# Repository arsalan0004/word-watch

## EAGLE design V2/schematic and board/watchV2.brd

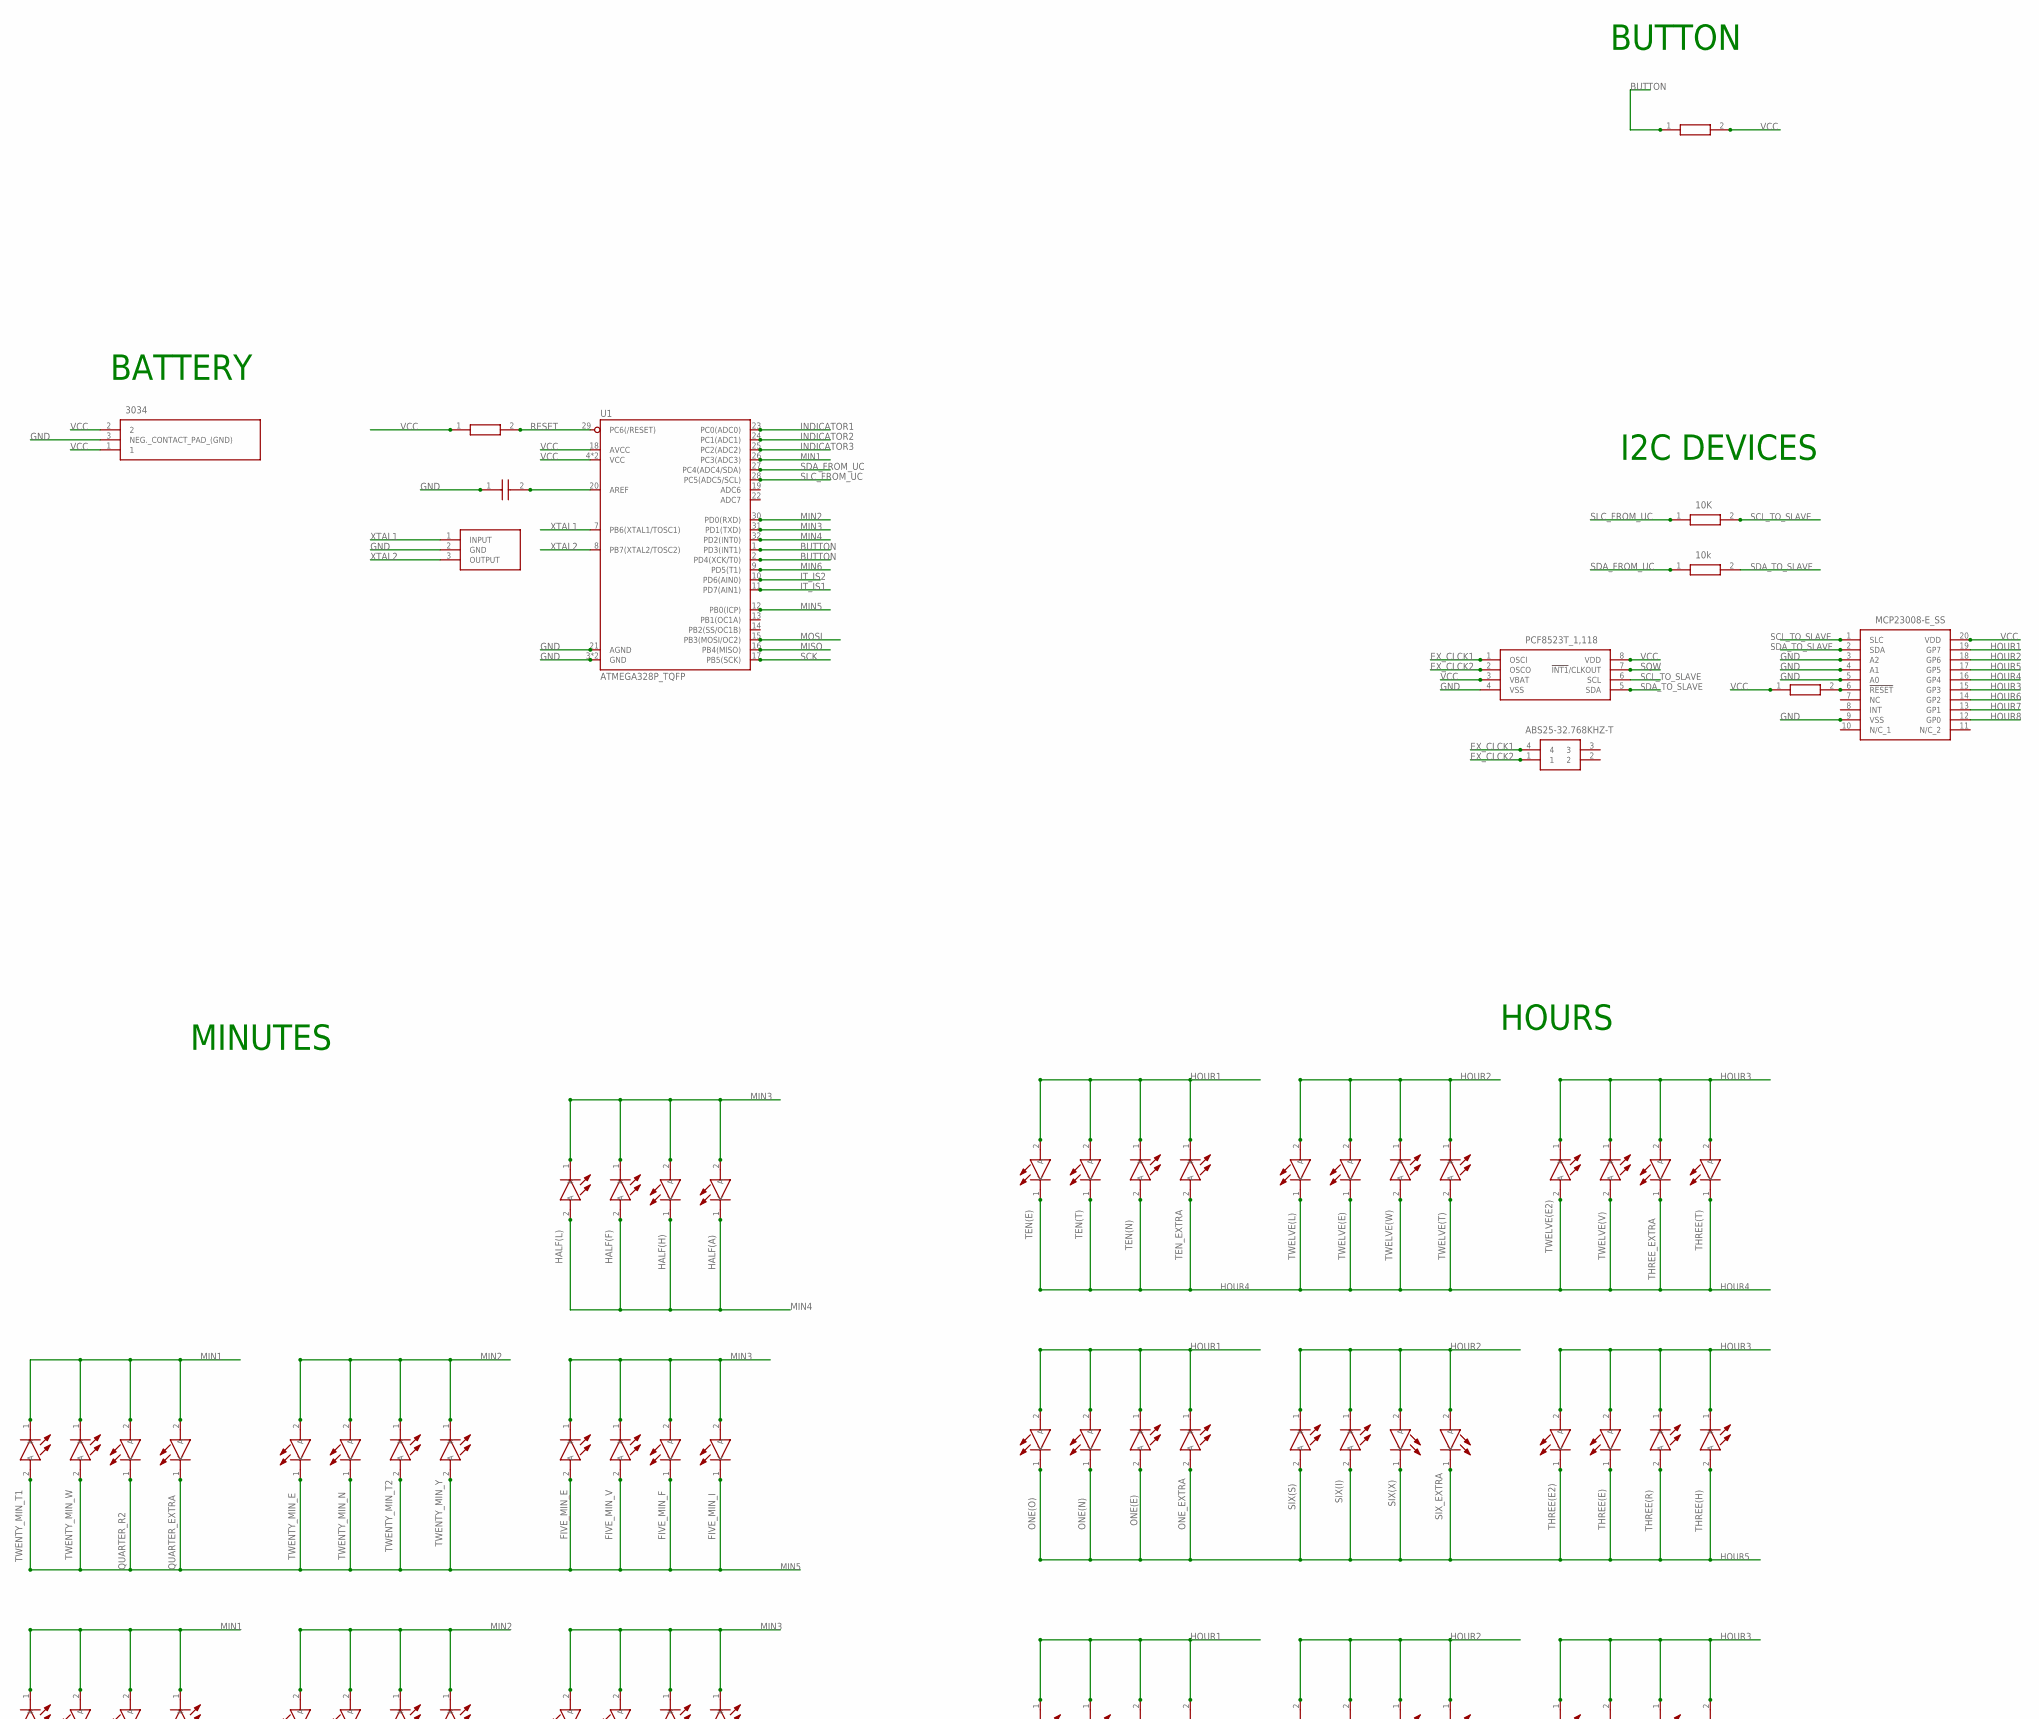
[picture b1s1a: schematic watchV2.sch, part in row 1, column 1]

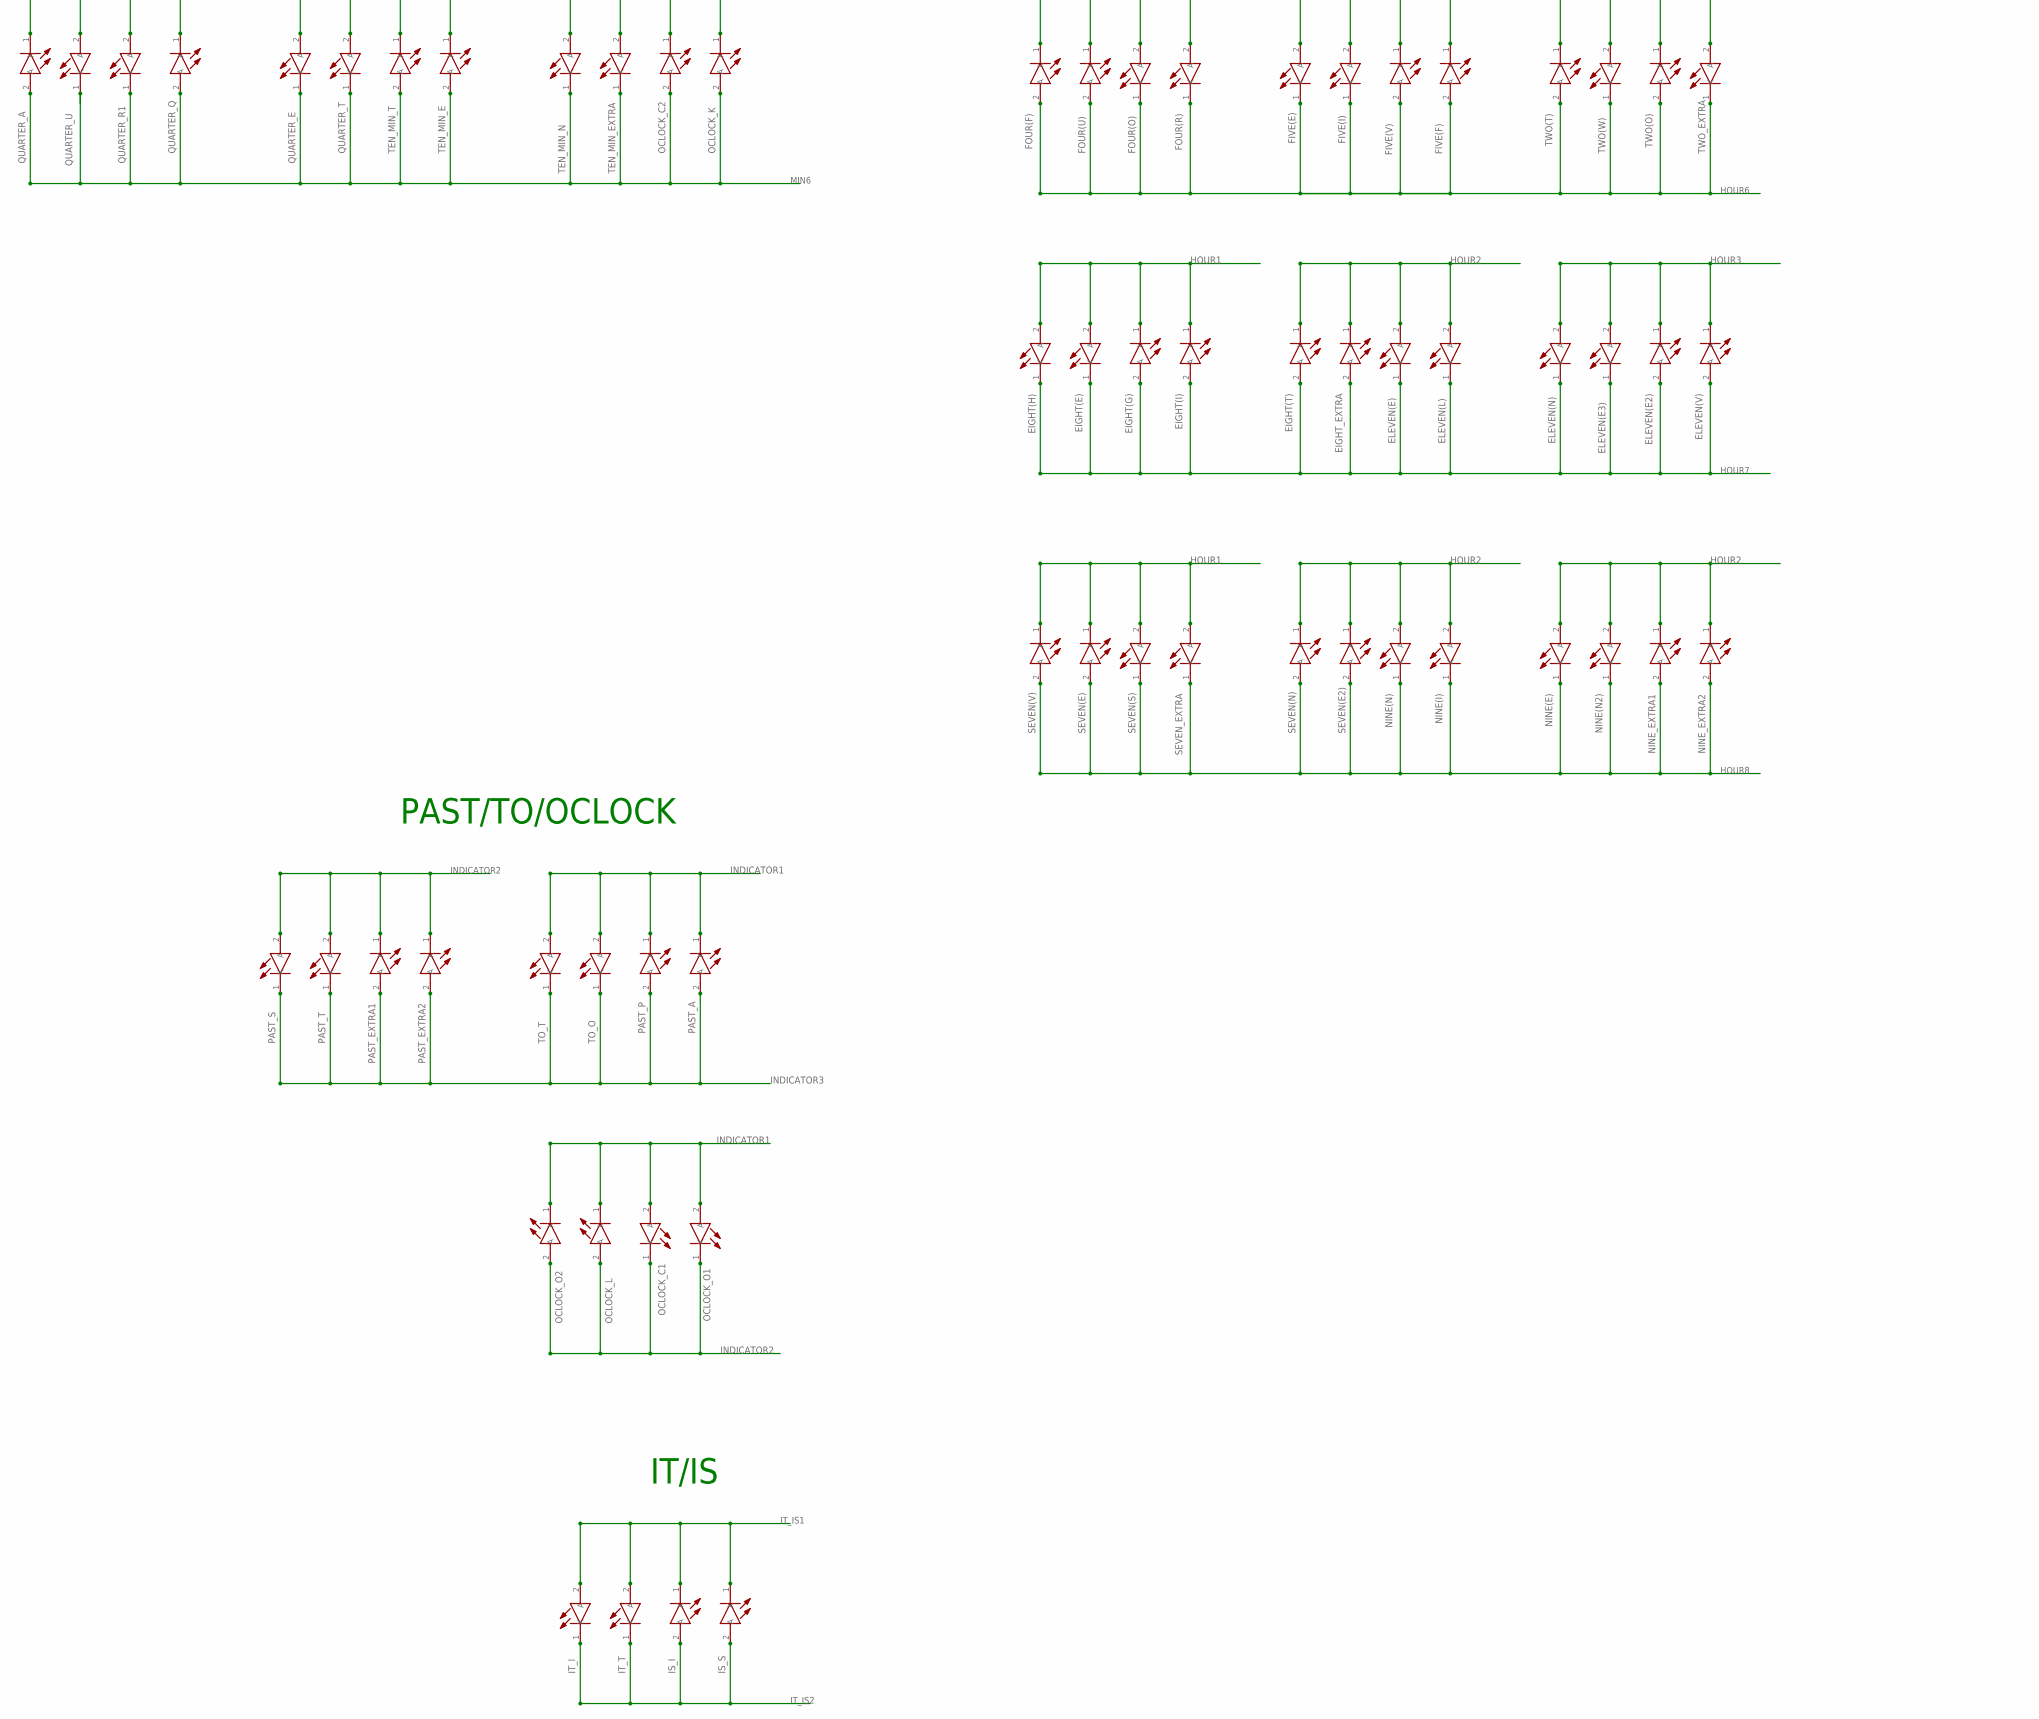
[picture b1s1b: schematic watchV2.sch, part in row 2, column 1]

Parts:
10K: RC0402FR-0722RL; RESC1005X40N
C1: C0402C104Z4VAC; CAPC1005X55N
EIGHT(E): APHHS1005CGCK; LEDC1005X60N
EIGHT(G): APHHS1005CGCK; LEDC1005X60N
EIGHT(H): APHHS1005CGCK; LEDC1005X60N
EIGHT(I): APHHS1005CGCK; LEDC1005X60N
EIGHT(T): APHHS1005CGCK; LEDC1005X60N
EIGHT_EXTRA: APHHS1005CGCK; LEDC1005X60N
ELEVEN(E2), ELEVEN(E3): APHHS1005CGCK; LEDC1005X60N
ELEVEN(E): APHHS1005CGCK; LEDC1005X60N
ELEVEN(L): APHHS1005CGCK; LEDC1005X60N
ELEVEN(N): APHHS1005CGCK; LEDC1005X60N
ELEVEN(V): APHHS1005CGCK; LEDC1005X60N
FIVE(E): APHHS1005CGCK; LEDC1005X60N
FIVE(F): APHHS1005CGCK; LEDC1005X60N
FIVE(I): APHHS1005CGCK; LEDC1005X60N
FIVE(V): APHHS1005CGCK; LEDC1005X60N
FIVE_MIN_E: APHHS1005CGCK; LEDC1005X60N
FIVE_MIN_F: APHHS1005CGCK; LEDC1005X60N
FIVE_MIN_I: APHHS1005CGCK; LEDC1005X60N
FIVE_MIN_V: APHHS1005CGCK; LEDC1005X60N
FOUR(F): APHHS1005CGCK; LEDC1005X60N
FOUR(O): APHHS1005CGCK; LEDC1005X60N
FOUR(R): APHHS1005CGCK; LEDC1005X60N
FOUR(U): APHHS1005CGCK; LEDC1005X60N
HALF(A): APHHS1005CGCK; LEDC1005X60N
HALF(F): APHHS1005CGCK; LEDC1005X60N
HALF(H): APHHS1005CGCK; LEDC1005X60N
HALF(L): APHHS1005CGCK; LEDC1005X60N
IC1: MCP23008-E_SS; SOP65P780X200-20N
IC2: CSTNE16M0VH3C000R0
IC3: PCF8523T_1,118; SOIC127P600X175-8N
IS_I: APHHS1005CGCK; LEDC1005X60N
IS_S: APHHS1005CGCK; LEDC1005X60N
IT_I: APHHS1005CGCK; LEDC1005X60N
IT_T: APHHS1005CGCK; LEDC1005X60N
NINE(E): APHHS1005CGCK; LEDC1005X60N
NINE(I): APHHS1005CGCK; LEDC1005X60N
NINE(N2): APHHS1005CGCK; LEDC1005X60N
NINE(N): APHHS1005CGCK; LEDC1005X60N
NINE_EXTRA1, NINE_EXTRA2: APHHS1005CGCK; LEDC1005X60N
OCLOCK_C1, OCLOCK_C2: APHHS1005CGCK; LEDC1005X60N
OCLOCK_K: APHHS1005CGCK; LEDC1005X60N
OCLOCK_L: APHHS1005CGCK; LEDC1005X60N
OCLOCK_O1, OCLOCK_O2: APHHS1005CGCK; LEDC1005X60N
ONE(E): APHHS1005CGCK; LEDC1005X60N
ONE(N): APHHS1005CGCK; LEDC1005X60N
ONE(O): APHHS1005CGCK; LEDC1005X60N
ONE_EXTRA: APHHS1005CGCK; LEDC1005X60N
PAST_A: APHHS1005CGCK; LEDC1005X60N
PAST_EXTRA1: 48ohm; LEDC1005X60N
PAST_EXTRA2: APHHS1005CGCK; LEDC1005X60N
PAST_P: 48ohm; LEDC1005X60N
PAST_S: APHHS1005CGCK; LEDC1005X60N
PAST_T: APHHS1005CGCK; LEDC1005X60N
QUARTER_A: APHHS1005CGCK; LEDC1005X60N
QUARTER_E: APHHS1005CGCK; LEDC1005X60N
QUARTER_EXTRA: APHHS1005CGCK; LEDC1005X60N
QUARTER_Q: APHHS1005CGCK; LEDC1005X60N
QUARTER_R1, QUARTER_R2: APHHS1005CGCK; LEDC1005X60N
QUARTER_T: APHHS1005CGCK; LEDC1005X60N
QUARTER_U: APHHS1005CGCK; LEDC1005X60N
RED1, RED2, RED5: RC0402FR-0722RL; RESC1005X40N
RED7: 10k; RESC1005X40N
SEVEN(E2): APHHS1005CGCK; LEDC1005X60N
SEVEN(E): APHHS1005CGCK; LEDC1005X60N
SEVEN(N): APHHS1005CGCK; LEDC1005X60N
SEVEN(S): APHHS1005CGCK; LEDC1005X60N
SEVEN(V): APHHS1005CGCK; LEDC1005X60N
SEVEN_EXTRA: APHHS1005CGCK; LEDC1005X60N
SIX(I): APHHS1005CGCK; LEDC1005X60N
SIX(S): APHHS1005CGCK; LEDC1005X60N
SIX(X): APHHS1005CGCK; LEDC1005X60N
SIX_EXTRA: APHHS1005CGCK; LEDC1005X60N
TEN(E): APHHS1005CGCK; LEDC1005X60N
TEN(N): APHHS1005CGCK; LEDC1005X60N
TEN(T): APHHS1005CGCK; LEDC1005X60N
TEN_EXTRA: APHHS1005CGCK; LEDC1005X60N
TEN_MIN_E: APHHS1005CGCK; LEDC1005X60N
TEN_MIN_EXTRA: APHHS1005CGCK; LEDC1005X60N
TEN_MIN_N: APHHS1005CGCK; LEDC1005X60N
TEN_MIN_T: APHHS1005CGCK; LEDC1005X60N
THREE(E2): APHHS1005CGCK; LEDC1005X60N
THREE(E): APHHS1005CGCK; LEDC1005X60N
THREE(H): APHHS1005CGCK; LEDC1005X60N
THREE(R): APHHS1005CGCK; LEDC1005X60N
THREE(T): APHHS1005CGCK; LEDC1005X60N
THREE_EXTRA: APHHS1005CGCK; LEDC1005X60N
TO_O: APHHS1005CGCK; LEDC1005X60N
TO_T: APHHS1005CGCK; LEDC1005X60N
TWELVE(E2): APHHS1005CGCK; LEDC1005X60N
TWELVE(E): APHHS1005CGCK; LEDC1005X60N
TWELVE(L): APHHS1005CGCK; LEDC1005X60N
TWELVE(T): APHHS1005CGCK; LEDC1005X60N
TWELVE(V): APHHS1005CGCK; LEDC1005X60N
TWELVE(W): APHHS1005CGCK; LEDC1005X60N
TWENTY_MIN_E: APHHS1005CGCK; LEDC1005X60N
TWENTY_MIN_N: APHHS1005CGCK; LEDC1005X60N
TWENTY_MIN_T1, TWENTY_MIN_T2: APHHS1005CGCK; LEDC1005X60N
TWENTY_MIN_W: APHHS1005CGCK; LEDC1005X60N
TWENTY_MIN_Y: APHHS1005CGCK; LEDC1005X60N
TWO(O): APHHS1005CGCK; LEDC1005X60N
TWO(T): APHHS1005CGCK; LEDC1005X60N
TWO(W): APHHS1005CGCK; LEDC1005X60N
TWO_EXTRA: APHHS1005CGCK; LEDC1005X60N
U1: ATMEGA328P_TQFP; TQFP32-08
U2: 3034
Y1: ABS25-32.768KHZ-T; ABS2532768KHZT

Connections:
BUTTON: RED1.1, U1.1 (PD3(INT1)), U1.2 (PD4(XCK/T0))
EX_CLCK1: IC3.1 (OSCI), Y1.4
EX_CLCK2: IC3.2 (OSCO), Y1.1
GND: C1.1, IC1.3 (A2), IC1.4 (A1), IC1.5 (A0), IC1.9 (VSS), IC2.2 (GND), IC3.4 (VSS), U1.3 (GND), U1.5 (GND), U1.21 (AGND), U2.3 (NEG._CONTACT_PAD_(GND))
HOUR1: EIGHT(E).2 (A), EIGHT(G).1 (K), EIGHT(H).2 (A), EIGHT(I).1 (K), FOUR(F).1 (K), FOUR(O).2 (A), FOUR(R).2 (A), FOUR(U).1 (K), IC1.19 (GP7), ONE(E).1 (K), ONE(N).2 (A), ONE(O).2 (A), ONE_EXTRA.1 (K), SEVEN(E).1 (K), SEVEN(S).2 (A), SEVEN(V).1 (K), SEVEN_EXTRA.2 (A), TEN(E).2 (A), TEN(N).1 (K), TEN(T).2 (A), TEN_EXTRA.1 (K)
HOUR2: EIGHT(T).1 (K), EIGHT_EXTRA.1 (K), ELEVEN(E).2 (A), ELEVEN(L).2 (A), FIVE(E).2 (A), FIVE(F).1 (K), FIVE(I).2 (A), FIVE(V).1 (K), IC1.18 (GP6), NINE(E).2 (A), NINE(I).2 (A), NINE(N2).2 (A), NINE(N).2 (A), NINE_EXTRA1.1 (K), NINE_EXTRA2.1 (K), SEVEN(E2).1 (K), SEVEN(N).1 (K), SIX(I).1 (K), SIX(S).1 (K), SIX(X).2 (A), SIX_EXTRA.2 (A), TWELVE(E).2 (A), TWELVE(L).2 (A), TWELVE(T).1 (K), TWELVE(W).1 (K)
HOUR3: ELEVEN(E2).1 (K), ELEVEN(E3).2 (A), ELEVEN(N).2 (A), ELEVEN(V).1 (K), IC1.15 (GP3), THREE(E2).2 (A), THREE(E).2 (A), THREE(H).1 (K), THREE(R).1 (K), THREE(T).2 (A), THREE_EXTRA.2 (A), TWELVE(E2).1 (K), TWELVE(V).1 (K), TWO(O).1 (K), TWO(T).1 (K), TWO(W).2 (A), TWO_EXTRA.2 (A)
HOUR4: IC1.16 (GP4), TEN(E).1 (K), TEN(N).2 (A), TEN(T).1 (K), TEN_EXTRA.2 (A), THREE(T).1 (K), THREE_EXTRA.1 (K), TWELVE(E2).2 (A), TWELVE(E).1 (K), TWELVE(L).1 (K), TWELVE(T).2 (A), TWELVE(V).2 (A), TWELVE(W).2 (A)
HOUR5: IC1.17 (GP5), ONE(E).2 (A), ONE(N).1 (K), ONE(O).1 (K), ONE_EXTRA.2 (A), SIX(I).2 (A), SIX(S).2 (A), SIX(X).1 (K), SIX_EXTRA.1 (K), THREE(E2).1 (K), THREE(E).1 (K), THREE(H).2 (A), THREE(R).2 (A)
HOUR6: FIVE(E).1 (K), FIVE(F).2 (A), FIVE(I).1 (K), FIVE(V).2 (A), FOUR(F).2 (A), FOUR(O).1 (K), FOUR(R).1 (K), FOUR(U).2 (A), IC1.14 (GP2), TWO(O).2 (A), TWO(T).2 (A), TWO(W).1 (K), TWO_EXTRA.1 (K)
HOUR7: EIGHT(E).1 (K), EIGHT(G).2 (A), EIGHT(H).1 (K), EIGHT(I).2 (A), EIGHT(T).2 (A), EIGHT_EXTRA.2 (A), ELEVEN(E2).2 (A), ELEVEN(E3).1 (K), ELEVEN(E).1 (K), ELEVEN(L).1 (K), ELEVEN(N).1 (K), ELEVEN(V).2 (A), IC1.13 (GP1)
HOUR8: IC1.12 (GP0), NINE(E).1 (K), NINE(I).1 (K), NINE(N2).1 (K), NINE(N).1 (K), NINE_EXTRA1.2 (A), NINE_EXTRA2.2 (A), SEVEN(E2).2 (A), SEVEN(E).2 (A), SEVEN(N).2 (A), SEVEN(S).1 (K), SEVEN(V).2 (A), SEVEN_EXTRA.1 (K)
INDICATOR1: OCLOCK_C1.2 (A), OCLOCK_L.1 (K), OCLOCK_O1.2 (A), OCLOCK_O2.1 (K), PAST_A.1 (K), PAST_P.1 (K), TO_O.2 (A), TO_T.2 (A), U1.23 (PC0(ADC0))
INDICATOR2: OCLOCK_C1.1 (K), OCLOCK_L.2 (A), OCLOCK_O1.1 (K), OCLOCK_O2.2 (A), PAST_EXTRA1.1 (K), PAST_EXTRA2.1 (K), PAST_S.2 (A), PAST_T.2 (A), U1.24 (PC1(ADC1))
INDICATOR3: PAST_A.2 (A), PAST_EXTRA1.2 (A), PAST_EXTRA2.2 (A), PAST_P.2 (A), PAST_S.1 (K), PAST_T.1 (K), TO_O.1 (K), TO_T.1 (K), U1.25 (PC2(ADC2))
IT_IS1: IS_I.1 (K), IS_S.1 (K), IT_I.2 (A), IT_T.2 (A), U1.11 (PD7(AIN1))
IT_IS2: IS_I.2 (A), IS_S.2 (A), IT_I.1 (K), IT_T.1 (K), U1.10 (PD6(AIN0))
MIN1: QUARTER_A.1 (K), QUARTER_EXTRA.2 (A), QUARTER_Q.1 (K), QUARTER_R1.2 (A), QUARTER_R2.2 (A), QUARTER_U.2 (A), TWENTY_MIN_T1.1 (K), TWENTY_MIN_W.1 (K), U1.26 (PC3(ADC3))
MIN2: QUARTER_E.2 (A), QUARTER_T.2 (A), TEN_MIN_E.1 (K), TEN_MIN_T.1 (K), TWENTY_MIN_E.2 (A), TWENTY_MIN_N.2 (A), TWENTY_MIN_T2.1 (K), TWENTY_MIN_Y.1 (K), U1.30 (PD0(RXD))
MIN3: FIVE_MIN_E.1 (K), FIVE_MIN_F.2 (A), FIVE_MIN_I.2 (A), FIVE_MIN_V.1 (K), HALF(A).2 (A), HALF(F).1 (K), HALF(H).2 (A), HALF(L).1 (K), OCLOCK_C2.1 (K), OCLOCK_K.1 (K), TEN_MIN_EXTRA.2 (A), TEN_MIN_N.2 (A), U1.31 (PD1(TXD))
MIN4: HALF(A).1 (K), HALF(F).2 (A), HALF(H).1 (K), HALF(L).2 (A), U1.32 (PD2(INT0))
MIN5: FIVE_MIN_E.2 (A), FIVE_MIN_F.1 (K), FIVE_MIN_I.1 (K), FIVE_MIN_V.2 (A), QUARTER_EXTRA.1 (K), QUARTER_R2.1 (K), TWENTY_MIN_E.1 (K), TWENTY_MIN_N.1 (K), TWENTY_MIN_T1.2 (A), TWENTY_MIN_T2.2 (A), TWENTY_MIN_W.2 (A), TWENTY_MIN_Y.2 (A), U1.12 (PB0(ICP))
MIN6: OCLOCK_C2.2 (A), OCLOCK_K.2 (A), QUARTER_A.2 (A), QUARTER_E.1 (K), QUARTER_Q.2 (A), QUARTER_R1.1 (K), QUARTER_T.1 (K), QUARTER_U.1 (K), TEN_MIN_E.2 (A), TEN_MIN_EXTRA.1 (K), TEN_MIN_N.1 (K), TEN_MIN_T.2 (A), U1.9 (PD5(T1))
MISO: U1.16 (PB4(MISO))
MOSI: U1.15 (PB3(MOSI/OC2))
unnamed: IC1.6 (!RESET), RED2.2
unnamed: C1.2, U1.20 (AREF)
RESET: RED5.2, U1.29 (PC6(/RESET))
SCK: U1.17 (PB5(SCK))
SCL_TO_SLAVE: 10K.2, IC1.1 (SLC), IC3.6 (SCL)
SDA_FROM_UC: RED7.1, U1.27 (PC4(ADC4/SDA))
SDA_TO_SLAVE: IC1.2 (SDA), IC3.5 (SDA), RED7.2
SLC_FROM_UC: 10K.1, U1.28 (PC5(ADC5/SCL))
SQW: IC3.7 (!INT1!/CLKOUT)
VCC: IC1.20 (VDD), IC3.3 (VBAT), IC3.8 (VDD), RED1.2, RED2.1, RED5.1, U1.4 (VCC), U1.6 (VCC), U1.18 (AVCC), U2.1, U2.2
XTAL1: IC2.1 (INPUT), U1.7 (PB6(XTAL1/TOSC1))
XTAL2: IC2.3 (OUTPUT), U1.8 (PB7(XTAL2/TOSC2))

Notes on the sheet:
HOURS
MINUTES
IT/IS
I2C DEVICES
BUTTON
BATTERY
PAST/TO/OCLOCK

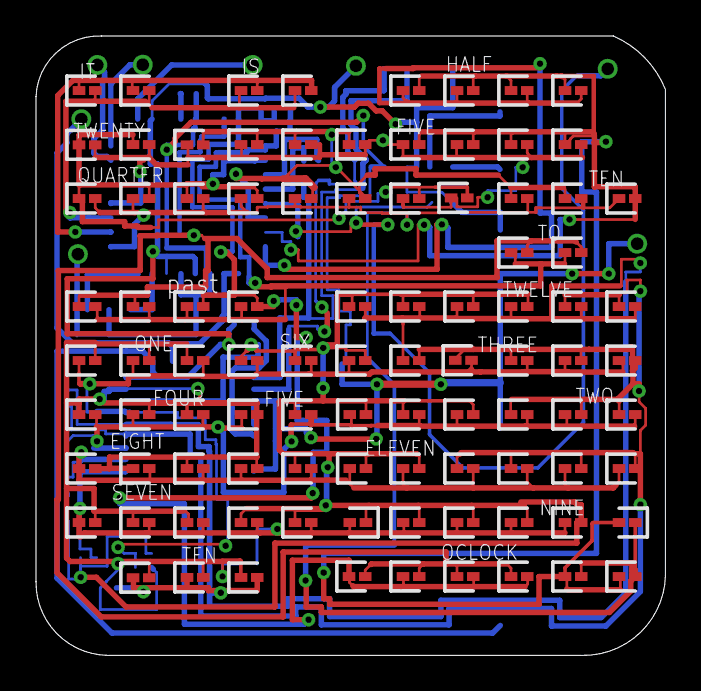
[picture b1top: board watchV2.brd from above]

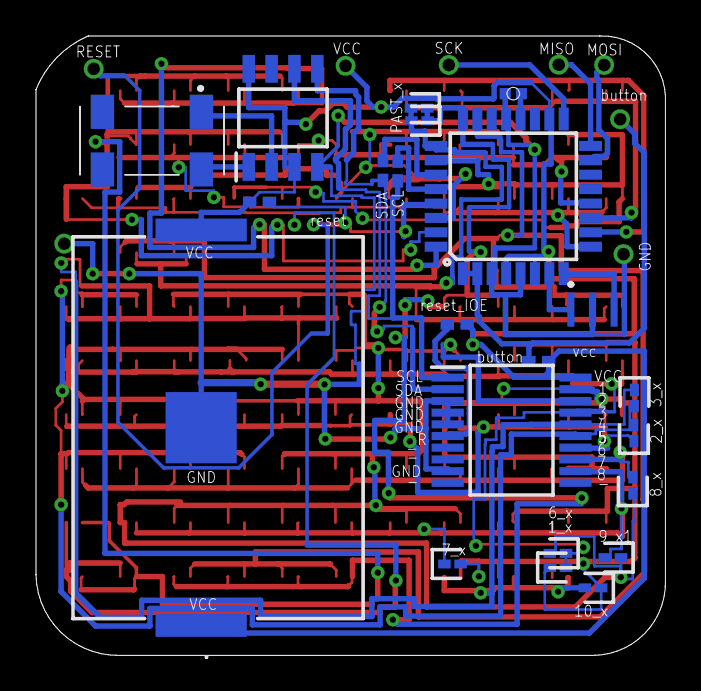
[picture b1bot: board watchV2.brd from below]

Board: 2 copper layers, 35.0 x 34.4 mm, 116 parts (22 on the bottom side), 33 nets.

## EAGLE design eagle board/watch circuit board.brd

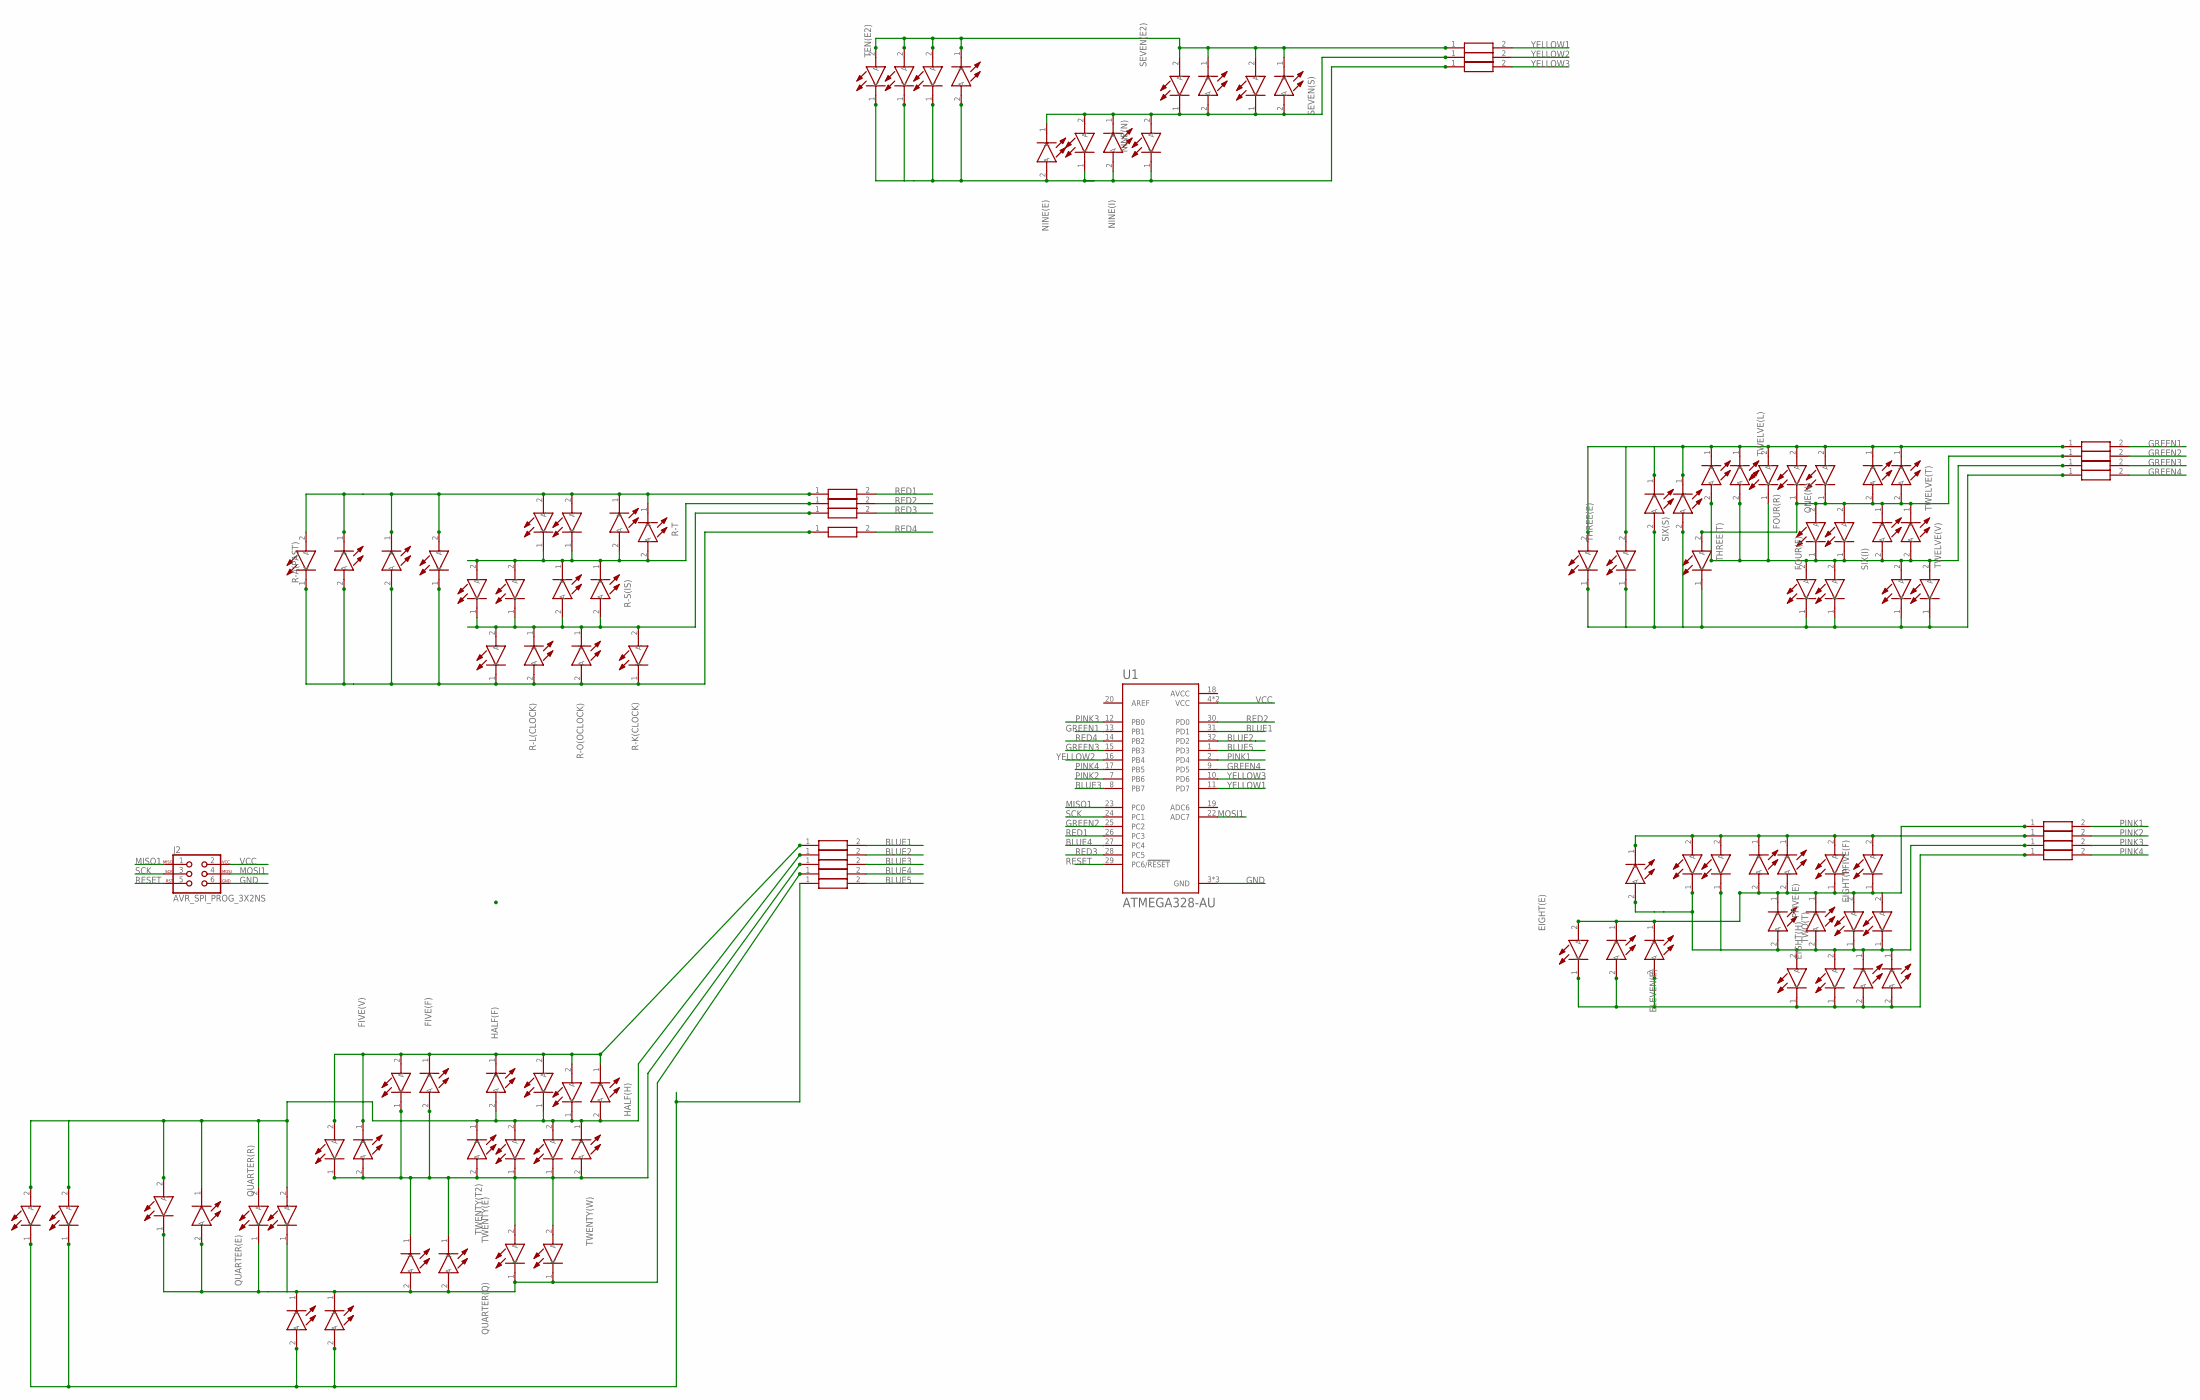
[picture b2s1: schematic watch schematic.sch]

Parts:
EIGHT(E): APHHS1005CGCK; LEDC1005X60N
EIGHT(G): APHHS1005CGCK; LEDC1005X60N
EIGHT(H): APHHS1005CGCK; LEDC1005X60N
EIGHT(I): APHHS1005CGCK; LEDC1005X60N
EIGHT(T): APHHS1005CGCK; LEDC1005X60N
ELEVEN(E2), ELEVEN(E3): APHHS1005CGCK; LEDC1005X60N
ELEVEN(E): APHHS1005CGCK; LEDC1005X60N
ELEVEN(L): APHHS1005CGCK; LEDC1005X60N
ELEVEN(N): APHHS1005CGCK; LEDC1005X60N
ELEVEN(V): APHHS1005CGCK; LEDC1005X60N
FIVE(E): APHHS1005CGCK; LEDC1005X60N
FIVE(F): APHHS1005CGCK; LEDC1005X60N
FIVE(I): APHHS1005CGCK; LEDC1005X60N
FIVE(V): APHHS1005CGCK; LEDC1005X60N
FOUR(F): APHHS1005CGCK; LEDC1005X60N
FOUR(O): APHHS1005CGCK; LEDC1005X60N
FOUR(R): APHHS1005CGCK; LEDC1005X60N
FOUR(U): APHHS1005CGCK; LEDC1005X60N
HALF(A): APHHS1005CGCK; LEDC1005X60N
HALF(F): APHHS1005CGCK; LEDC1005X60N
HALF(H): APHHS1005CGCK; LEDC1005X60N
HALF(L): APHHS1005CGCK; LEDC1005X60N
J2: AVR_SPI_PROG_3X2NS; 2X3-NS
NINE(E): APHHS1005CGCK; LEDC1005X60N
NINE(I): APHHS1005CGCK; LEDC1005X60N
NINE(N2): APHHS1005CGCK; LEDC1005X60N
NINE(N): APHHS1005CGCK; LEDC1005X60N
ONE(E): APHHS1005CGCK; LEDC1005X60N
ONE(N): APHHS1005CGCK; LEDC1005X60N
ONE(O): APHHS1005CGCK; LEDC1005X60N
PFIVE(E): APHHS1005CGCK; LEDC1005X60N
PFIVE(F): APHHS1005CGCK; LEDC1005X60N
PFIVE(I): APHHS1005CGCK; LEDC1005X60N
PFIVE(V): APHHS1005CGCK; LEDC1005X60N
QUARTER(A): APHHS1005CGCK; LEDC1005X60N
QUARTER(E): APHHS1005CGCK; LEDC1005X60N
QUARTER(Q): APHHS1005CGCK; LEDC1005X60N
QUARTER(R2): APHHS1005CGCK; LEDC1005X60N
QUARTER(R): APHHS1005CGCK; LEDC1005X60N
QUARTER(T): APHHS1005CGCK; LEDC1005X60N
QUARTER(U): APHHS1005CGCK; LEDC1005X60N
R1, R2, R3, R4, R5, R6, R8, R9, R10, R11, R12, R14, R15, R16, R17, R18, R20, R21, R22, R24: RC0402FR-0722RL; RESC1005X40N
R-A(PAST): APHHS1005CGCK; LEDC1005X60N
R-C2(CLOCK): APHHS1005CGCK; LEDC1005X60N
R-C(OCLOCK): APHHS1005CGCK; LEDC1005X60N
R-I: APHHS1005CGCK; LEDC1005X60N
R-I(IS): APHHS1005CGCK; LEDC1005X60N
R-K(CLOCK): APHHS1005CGCK; LEDC1005X60N
R-L(CLOCK): APHHS1005CGCK; LEDC1005X60N
R-O(OCLOCK): APHHS1005CGCK; LEDC1005X60N
R-O(TO): APHHS1005CGCK; LEDC1005X60N
R-OH(OCLOCK)1: APHHS1005CGCK; LEDC1005X60N
R-P(PAST): APHHS1005CGCK; LEDC1005X60N
R-S(IS): APHHS1005CGCK; LEDC1005X60N
R-S(PAST): APHHS1005CGCK; LEDC1005X60N
R-T: APHHS1005CGCK; LEDC1005X60N
R-T(PAST): APHHS1005CGCK; LEDC1005X60N
R-T(TO): APHHS1005CGCK; LEDC1005X60N
SEVEN(E2): APHHS1005CGCK; LEDC1005X60N
SEVEN(E): APHHS1005CGCK; LEDC1005X60N
SEVEN(N): APHHS1005CGCK; LEDC1005X60N
SEVEN(S): APHHS1005CGCK; LEDC1005X60N
SEVEN(V): APHHS1005CGCK; LEDC1005X60N
SIX(I): APHHS1005CGCK; LEDC1005X60N
SIX(S): APHHS1005CGCK; LEDC1005X60N
SIX(X): APHHS1005CGCK; LEDC1005X60N
TEN(E2): APHHS1005CGCK; LEDC1005X60N
TEN(E): APHHS1005CGCK; LEDC1005X60N
TEN(N2): APHHS1005CGCK; LEDC1005X60N
TEN(N): APHHS1005CGCK; LEDC1005X60N
TEN(T2): APHHS1005CGCK; LEDC1005X60N
TEN(T): APHHS1005CGCK; LEDC1005X60N
THREE(E2): APHHS1005CGCK; LEDC1005X60N
THREE(E): APHHS1005CGCK; LEDC1005X60N
THREE(R): APHHS1005CGCK; LEDC1005X60N
THREE(T): APHHS1005CGCK; LEDC1005X60N
TWELVE(E2): APHHS1005CGCK; LEDC1005X60N
TWELVE(E): APHHS1005CGCK; LEDC1005X60N
TWELVE(L): APHHS1005CGCK; LEDC1005X60N
TWELVE(T): APHHS1005CGCK; LEDC1005X60N
TWELVE(V): APHHS1005CGCK; LEDC1005X60N
TWELVE(W): APHHS1005CGCK; LEDC1005X60N
TWENTY(E): APHHS1005CGCK; LEDC1005X60N
TWENTY(N): APHHS1005CGCK; LEDC1005X60N
TWENTY(T2): APHHS1005CGCK; LEDC1005X60N
TWENTY(T): APHHS1005CGCK; LEDC1005X60N
TWENTY(W): APHHS1005CGCK; LEDC1005X60N
TWENTY(Y): APHHS1005CGCK; LEDC1005X60N
TWO(O): APHHS1005CGCK; LEDC1005X60N
TWO(T): APHHS1005CGCK; LEDC1005X60N
TWO(W): APHHS1005CGCK; LEDC1005X60N
U1: ATMEGA328-AU; QFP80P900X900X120-32N

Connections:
AVCC: U1.18 (AVCC)
BLUE1: R1.2, U1.31 (PD1)
BLUE2: R2.2, U1.32 (PD2)
BLUE3: R3.2, U1.8 (PB7)
BLUE4: R4.2, U1.27 (PC4)
BLUE5: R6.2, U1.1 (PD3)
GND: J2.6, U1.3 (GND), U1.5 (GND), U1.21 (GND)
GREEN1: R8.2, U1.13 (PB1)
GREEN2: R9.2, U1.25 (PC2)
GREEN3: R10.2, U1.15 (PB3)
GREEN4: R12.2, U1.9 (PD5)
IT/IS1: FIVE(E).2 (A), FIVE(F).1 (K), FIVE(I).2 (A), FIVE(V).1 (K), HALF(A).2 (A), HALF(F).1 (K), HALF(H).1 (K), HALF(L).2 (A), R1.1
IT/IS4: R11.1, SEVEN(E2).2 (A), SEVEN(E).2 (A), SEVEN(N).1 (K), SEVEN(S).1 (K), SEVEN(V).1 (K), TEN(E2).2 (A), TEN(N2).2 (A), TEN(T2).2 (A)
MISO1: J2.1, U1.23 (PC0)
MOSI1: J2.4, U1.22 (ADC7)
unnamed: HALF(A).1 (K), HALF(F).2 (A), HALF(H).2 (A), HALF(L).1 (K), QUARTER(E).1 (K), QUARTER(R2).2 (A), QUARTER(R).2 (A), QUARTER(T).2 (A), R2.1, TEN(E).2 (A), TEN(N).2 (A), TWENTY(E).1 (K), TWENTY(N).2 (A), TWENTY(T).2 (A), TWENTY(W).1 (K)
unnamed: FOUR(F).2 (A), FOUR(O).2 (A), FOUR(R).2 (A), FOUR(U).2 (A), ONE(E).1 (K), ONE(N).1 (K), ONE(O).1 (K), R10.1, SIX(I).2 (A), SIX(X).2 (A), TWELVE(E2).2 (A), TWELVE(V).2 (A)
unnamed: ELEVEN(E3).2 (A), ELEVEN(N).2 (A), PFIVE(E).1 (K), PFIVE(F).2 (A), PFIVE(I).2 (A), PFIVE(V).1 (K), R14.1, TWO(O).1 (K)
unnamed: EIGHT(E).1 (K), EIGHT(H).1 (K), EIGHT(T).1 (K), ELEVEN(E2).2 (A), ELEVEN(E).2 (A), ELEVEN(L).2 (A), ELEVEN(V).2 (A), R21.1
unnamed: NINE(E).2 (A), SEVEN(N).2 (A), TEN(E2).1 (K), TEN(N2).1 (K), TEN(T2).1 (K)
unnamed: NINE(I).2 (A), NINE(N2).1 (K), NINE(N).1 (K), R24.1
unnamed: R20.1, R-A(PAST).2 (A), R-C2(CLOCK).1 (K), R-C(OCLOCK).1 (K), R-K(CLOCK).1 (K), R-L(CLOCK).2 (A), R-O(OCLOCK).2 (A), R-OH(OCLOCK)1.1 (K), R-P(PAST).2 (A)
unnamed: FOUR(R).1 (K), FOUR(U).1 (K), ONE(E).2 (A), R8.1, THREE(E2).2 (A), THREE(E).2 (A), THREE(R).1 (K), THREE(T).1 (K), TWELVE(E).2 (A), TWELVE(L).2 (A), TWELVE(T).1 (K), TWELVE(W).1 (K)
unnamed: ONE(N).2 (A), ONE(O).2 (A), R9.1, SIX(S).2 (A), TWELVE(E2).1 (K), TWELVE(E).1 (K), TWELVE(L).1 (K), TWELVE(T).2 (A), TWELVE(V).1 (K), TWELVE(W).2 (A)
unnamed: FOUR(F).1 (K), FOUR(O).1 (K), R12.1, SIX(I).1 (K), SIX(S).1 (K), SIX(X).1 (K), THREE(E2).1 (K), THREE(E).1 (K), THREE(R).2 (A), THREE(T).2 (A)
unnamed: EIGHT(E).2 (A), EIGHT(G).2 (A), EIGHT(I).2 (A), ELEVEN(E).1 (K), ELEVEN(L).1 (K), PFIVE(E).2 (A), PFIVE(F).1 (K), PFIVE(I).1 (K), PFIVE(V).2 (A), R5.1, TWO(T).1 (K), TWO(W).1 (K)
unnamed: R18.1, R-C2(CLOCK).2 (A), R-I(IS).2 (A), R-K(CLOCK).2 (A), R-L(CLOCK).1 (K), R-O(OCLOCK).1 (K), R-S(IS).2 (A), R-S(PAST).1 (K), R-T(PAST).1 (K)
unnamed: R16.1, R-A(PAST).1 (K), R-C(OCLOCK).2 (A), R-I.1 (K), R-O(TO).2 (A), R-OH(OCLOCK)1.2 (A), R-P(PAST).1 (K), R-T.1 (K), R-T(TO).2 (A)
unnamed: R17.1, R-I.2 (A), R-I(IS).1 (K), R-O(TO).1 (K), R-S(IS).1 (K), R-S(PAST).2 (A), R-T.2 (A), R-T(PAST).2 (A), R-T(TO).1 (K)
unnamed: FIVE(E).1 (K), FIVE(F).2 (A), FIVE(I).1 (K), FIVE(V).2 (A), QUARTER(Q).1 (K), QUARTER(U).1 (K), R3.1, TWENTY(E).2 (A), TWENTY(N).1 (K), TWENTY(T2).2 (A), TWENTY(T).1 (K), TWENTY(W).2 (A), TWENTY(Y).2 (A)
unnamed: QUARTER(A).2 (A), R6.1, TEN(E).1 (K), TEN(N).1 (K), TEN(T).2 (A)
unnamed: QUARTER(A).1 (K), QUARTER(E).2 (A), QUARTER(Q).2 (A), QUARTER(R2).1 (K), QUARTER(R).1 (K), QUARTER(T).1 (K), QUARTER(U).2 (A), R4.1, TEN(T).1 (K), TWENTY(T2).1 (K), TWENTY(Y).1 (K)
unnamed: EIGHT(G).1 (K), EIGHT(H).2 (A), EIGHT(I).1 (K), EIGHT(T).2 (A), ELEVEN(E2).1 (K), ELEVEN(E3).1 (K), ELEVEN(N).1 (K), ELEVEN(V).1 (K), R15.1, TWO(O).2 (A), TWO(T).2 (A), TWO(W).2 (A)
unnamed: NINE(E).1 (K), NINE(I).1 (K), NINE(N2).2 (A), NINE(N).2 (A), R22.1, SEVEN(E2).1 (K), SEVEN(E).1 (K), SEVEN(S).2 (A), SEVEN(V).2 (A)
PINK1: R5.2, U1.2 (PD4)
PINK2: R14.2, U1.7 (PB6)
PINK3: R15.2, U1.12 (PB0)
PINK4: R21.2, U1.17 (PB5)
RED1: R16.2, U1.26 (PC3)
RED2: R17.2, U1.30 (PD0)
RED3: R18.2, U1.28 (PC5)
RED4: R20.2, U1.14 (PB2)
RESET: J2.5, U1.29 (PC6/!RESET)
SCK: J2.3, U1.24 (PC1)
VCC: J2.2, U1.4 (VCC), U1.6 (VCC)
YELLOW1: R11.2, U1.11 (PD7)
YELLOW2: R22.2, U1.16 (PB4)
YELLOW3: R24.2, U1.10 (PD6)

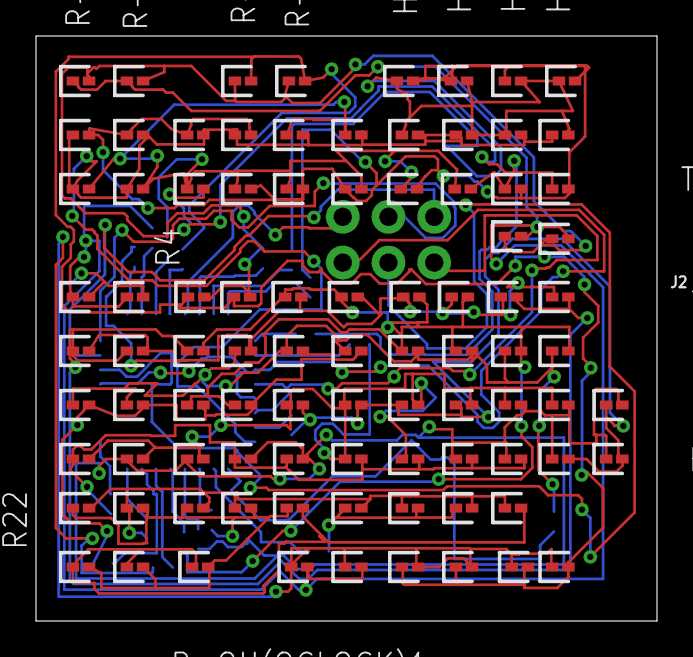
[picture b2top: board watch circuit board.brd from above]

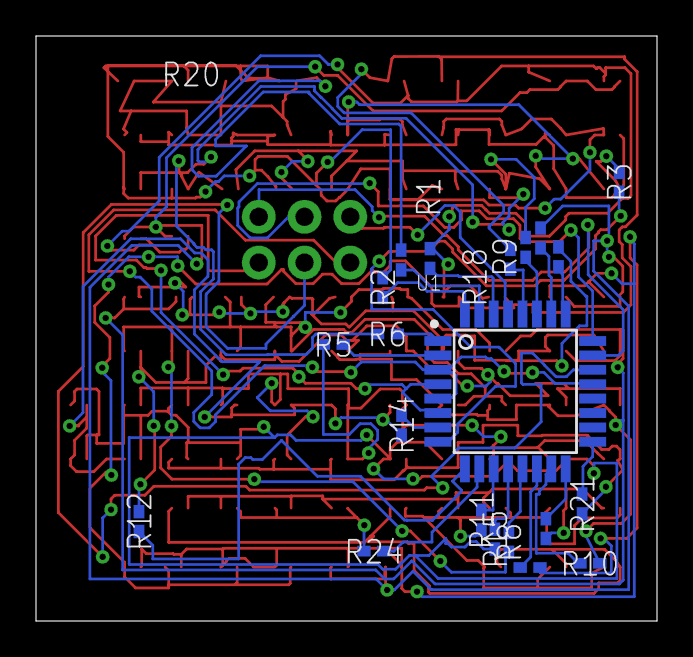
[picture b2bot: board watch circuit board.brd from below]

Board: 2 copper layers, 34.5 x 32.5 mm, 112 parts (21 on the bottom side), 47 nets.

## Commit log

2020-02-18 functions for glowing letters created
2020-02-19 Update CurrentSketch.ino
    added some button functionality
2020-02-21 Update CurrentSketch.ino
    1/2 of code for changing time is complete
2020-02-23 Update CurrentSketch.ino
    set up pointer system for managing time changes.
2020-02-26 First Draft complete
    complete, however has not been run on atmega328au yet. Will likely requre modifications after it has been run for the first time.
2021-01-06 top layer is immaculate
    wired an immaculate top-layer on the watch board
2021-01-19 Moved old version of the watch into the folder 'V1' and started working on the new watch code, which is being developed inside folder 'V2'
2021-01-20 created functions for setting MCP23008 pins as outputs/inputs and setting them as HIGH/LOW
    :wq
2021-01-20 fixed syntax issues so the document would compile
2021-01-21 addeed all 'hour functions' and included the new schematic and board from Eagle
2021-01-22 added all minute functions
2021-01-25 finished 'Indicator_Functions.h' and completed 'glow_time' function in 'Main.cpp'

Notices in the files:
parts and their libraries:
SparkFun-IC-Microcontroller: Licensing: Creative Commons ShareAlike 4.0 International - https://creativecommons.org/licenses/by-sa/4.0
